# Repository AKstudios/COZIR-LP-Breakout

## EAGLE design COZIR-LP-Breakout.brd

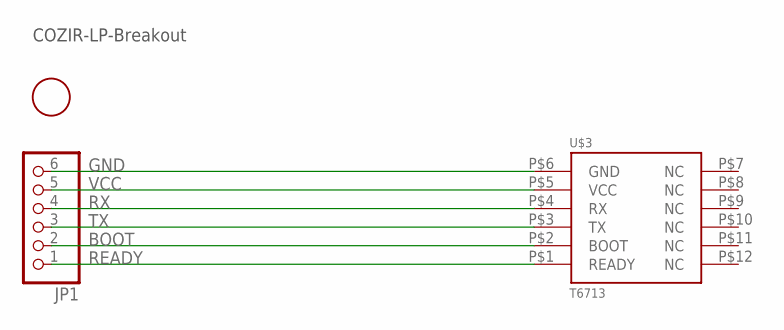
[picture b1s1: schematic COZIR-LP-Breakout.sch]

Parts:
JP1: PINHD-1X6; 1X06
U$2: FIDUCIAL; FIDUCIAL_1MM
U$3: T6713; RECEPTACLE_1.27MM_2X6

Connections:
BOOT: JP1.2, U$3.P$2 (BOOT)
GND: JP1.6, U$3.P$6 (GND)
READY: JP1.1, U$3.P$1 (READY)
RX: JP1.4, U$3.P$4 (RX)
TX: JP1.3, U$3.P$3 (TX)
VCC: JP1.5, U$3.P$5 (VCC)

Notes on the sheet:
COZIR-LP-Breakout

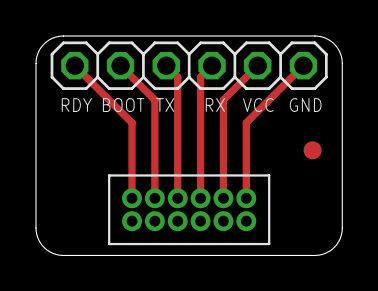
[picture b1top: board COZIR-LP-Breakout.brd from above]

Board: 2 copper layers, 17.0 x 12.2 mm, 3 parts (0 on the bottom side), 6 nets.

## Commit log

2017-05-14 :neckbeard: Added .gitattributes & .gitignore files
2017-05-14 Uploaded EAGLE files
